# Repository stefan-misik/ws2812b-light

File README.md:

# WS2812b Christmas Lights

This is a simple WS2812b Christmas lights controller using ATtiny85 microcontroller.

## Hardware

## Results

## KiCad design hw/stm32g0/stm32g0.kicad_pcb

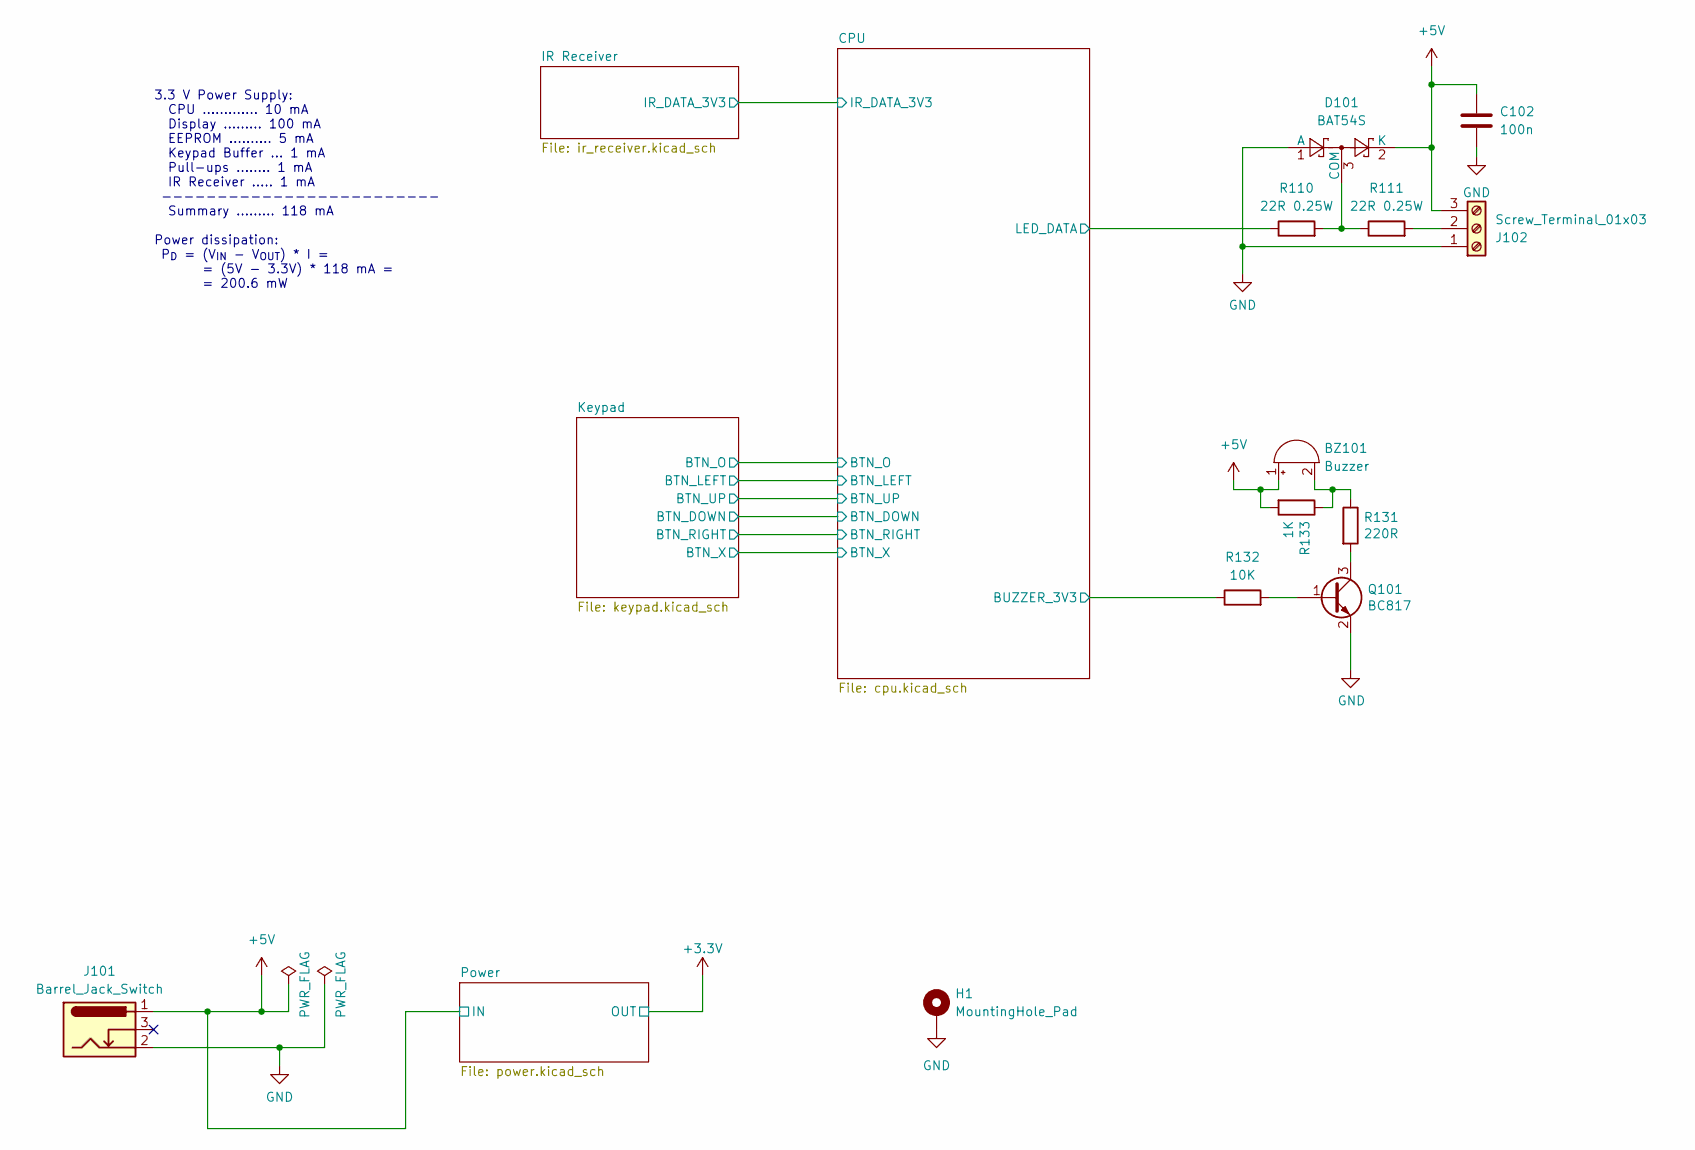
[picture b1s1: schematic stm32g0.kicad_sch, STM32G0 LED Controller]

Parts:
BZ101: Buzzer; Buzzer_Stacked
C102: 100n; C_0805_2012Metric_Pad1.18x1.45mm_HandSolder
D101: BAT54S; SOT-23_Handsoldering
H1: MountingHole_Pad; MountingHole_2.5mm_Pad_TopBottom
J101: Barrel_Jack_Switch; BarrelJack_GCT_DCJ200-10-A_Horizontal
J102: Screw_Terminal_01x03; TerminalBlock_Phoenix_MKDS-1,5-3_1x03_P5.00mm_Horizontal
Q101: BC817; SOT-23_Handsoldering
R110, R111: 22R 0.25W; R_1206_3216Metric_Pad1.30x1.75mm_HandSolder
R131: 220R; R_0805_2012Metric_Pad1.20x1.40mm_HandSolder
R132: 10K; R_0805_2012Metric_Pad1.20x1.40mm_HandSolder
R133: 1K; R_0805_2012Metric_Pad1.20x1.40mm_HandSolder

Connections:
+5V: BZ101.1 (+), C102.1, D101.2 (K), J101.1, J102.3, R133.2; also elsewhere on the board
/CPU/BUZZER_3V3: R132.1; also elsewhere on the board
/CPU/LED_DATA: R110.1; also elsewhere on the board
GND: C102.2, D101.1 (A), H1.1, J101.2, J102.1, Q101.2 (E); also elsewhere on the board
unnamed: BZ101.2 (-), R131.1, R133.1
unnamed: D101.3 (COM), R110.2, R111.1
unnamed: J102.2, R111.2
unnamed: Q101.1 (B), R132.2
unnamed: Q101.3 (C), R131.2

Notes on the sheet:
3.3 V Power Supply: CPU ............. 10 mA Display ......... 100 mA EEPROM .......... 5 mA Keypad Buffer ... 1 mA Pull-ups ........ 1 mA IR Receiver ..... 1 mA ------------------------- Summary ......... 118 mA Power dissipation: P_{D} = (V_{IN} - V_{OUT}) * I = = (5V - 3.3V) * 118 mA = = 200.6 mW

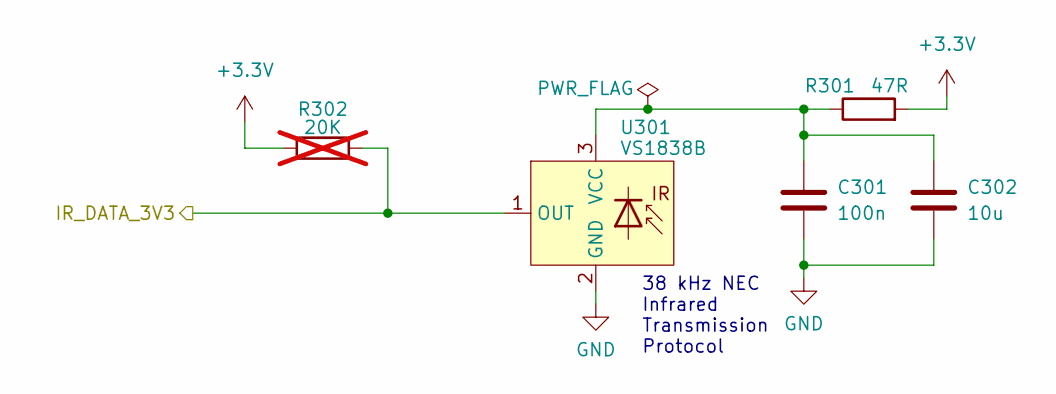
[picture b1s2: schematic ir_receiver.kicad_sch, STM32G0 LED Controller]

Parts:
C301: 100n; C_0805_2012Metric_Pad1.18x1.45mm_HandSolder
C302: 10u; C_1206_3216Metric_Pad1.33x1.80mm_HandSolder
R301: 47R; R_0805_2012Metric_Pad1.20x1.40mm_HandSolder
R302: 20K; R_0805_2012Metric_Pad1.20x1.40mm_HandSolder; not fitted
U301: VS1838B; PinSocket_1x03_P2.54mm_Vertical

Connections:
+3.3V: R301.2, R302.2; also elsewhere on the board
/CPU/IR_DATA_3V3: R302.1, U301.1 (OUT); also elsewhere on the board
GND: C301.2, C302.2, U301.2 (GND); also elsewhere on the board
unnamed: C301.1, C302.1, R301.1, U301.3 (VCC)

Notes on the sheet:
38 kHz NEC Infrared Transmission Protocol

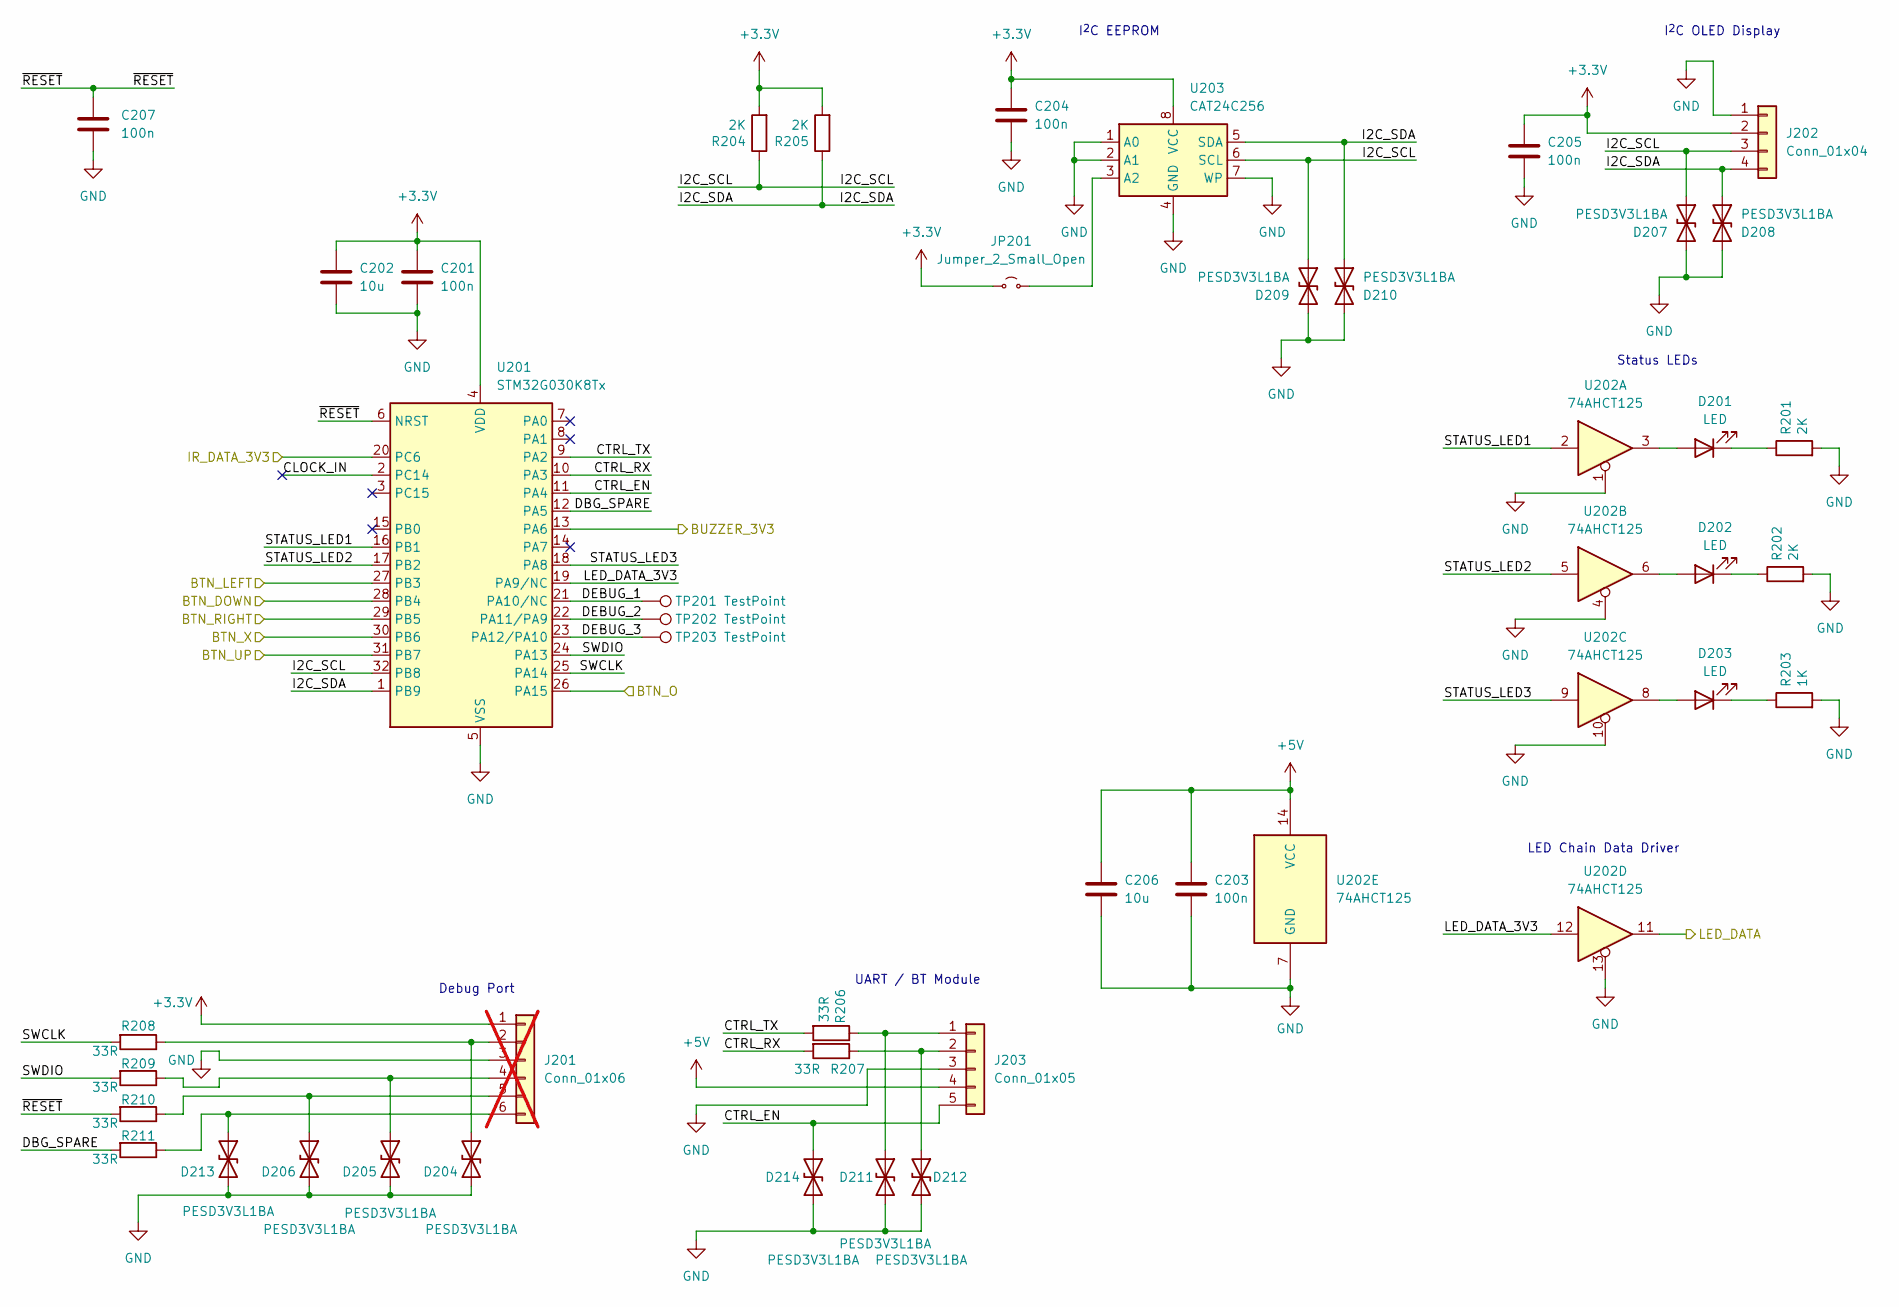
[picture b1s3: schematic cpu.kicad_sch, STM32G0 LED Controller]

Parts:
C201, C203, C204, C205, C207: 100n; C_0805_2012Metric_Pad1.18x1.45mm_HandSolder
C202, C206: 10u; C_1206_3216Metric_Pad1.33x1.80mm_HandSolder
D201, D202, D203: LED; LED_0805_2012Metric_Pad1.15x1.40mm_HandSolder
D204, D205, D206, D207, D208, D209, D210, D211, D212, D213, D214: PESD3V3L1BA; D_SOD-323_HandSoldering
J201: Conn_01x06; PinHeader_1x06_P2.54mm_Vertical; not fitted
J202: Conn_01x04; PinSocket_1x04_P2.54mm_Vertical
J203: Conn_01x05; PinSocket_1x05_P2.54mm_Vertical
JP201: Jumper_2_Small_Open; SolderJumper-2_P1.3mm_Open_RoundedPad1.0x1.5mm
R201, R202, R204, R205: 2K; R_0805_2012Metric_Pad1.20x1.40mm_HandSolder
R203: 1K; R_0805_2012Metric_Pad1.20x1.40mm_HandSolder
R206, R207, R208, R209, R210, R211: 33R; R_0805_2012Metric_Pad1.20x1.40mm_HandSolder
TP201, TP202, TP203: TestPoint; TestPoint_Pad_1.0x1.0mm
U201: STM32G030K8Tx; LQFP-32_7x7mm_P0.8mm
U202: 74AHCT125; SOIC-14_3.9x8.7mm_P1.27mm
U203: CAT24C256; DIP-8_W7.62mm_Socket_Stacked_SOIC-8_3.9x4.9mm_P1.27mm

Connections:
+3.3V: C201.1, C202.1, C204.1, C205.1, J201.1, J202.2, JP201.1 (A), R204.2, R205.2, U201.4 (VDD), U203.8 (VCC); also elsewhere on the board
+5V: C203.1, C206.1, J203.4, U202.14 (VCC); also elsewhere on the board
/CPU/BTN_DOWN: U201.28 (PB4); also elsewhere on the board
/CPU/BTN_LEFT: U201.27 (PB3); also elsewhere on the board
/CPU/BTN_O: U201.26 (PA15); also elsewhere on the board
/CPU/BTN_RIGHT: U201.29 (PB5); also elsewhere on the board
/CPU/BTN_UP: U201.31 (PB7); also elsewhere on the board
/CPU/BTN_X: U201.30 (PB6); also elsewhere on the board
/CPU/BUZZER_3V3: U201.13 (PA6); also elsewhere on the board
/CPU/CLOCK_IN: U201.2 (PC14)
/CPU/CTRL_EN: D214.1 (A1), J203.5, U201.11 (PA4)
/CPU/CTRL_RX: R207.2, U201.10 (PA3)
/CPU/CTRL_TX: R206.2, U201.9 (PA2)
/CPU/DBG_SPARE: R211.2, U201.12 (PA5)
/CPU/DEBUG_1: TP201.1, U201.21 (PA10/NC)
/CPU/DEBUG_2: TP202.1, U201.22 (PA11/PA9)
/CPU/DEBUG_3: TP203.1, U201.23 (PA12/PA10)
/CPU/I2C_SCL: D207.1 (A1), D209.1 (A1), J202.3, R204.1, U201.32 (PB8), U203.6 (SCL)
/CPU/I2C_SDA: D208.1 (A1), D210.1 (A1), J202.4, R205.1, U201.1 (PB9), U203.5 (SDA)
/CPU/IR_DATA_3V3: U201.20 (PC6); also elsewhere on the board
/CPU/LED_DATA: U202.11; also elsewhere on the board
/CPU/LED_DATA_3V3: U201.19 (PA9/NC), U202.12
/CPU/STATUS_LED1: U201.16 (PB1), U202.2
/CPU/STATUS_LED2: U201.17 (PB2), U202.5
/CPU/STATUS_LED3: U201.18 (PA8), U202.9
/CPU/SWCLK: R208.2, U201.25 (PA14)
/CPU/SWDIO: R209.2, U201.24 (PA13)
/CPU/~RESET: C207.1, R210.2, U201.6 (NRST)
GND: C201.2, C202.2, C203.2, C204.2, C205.2, C206.2, C207.2, D204.2 (A2), D205.2 (A2), D206.2 (A2), D207.2 (A2), D208.2 (A2), D209.2 (A2), D210.2 (A2), D211.2 (A2), D212.2 (A2), D213.2 (A2), D214.2 (A2), J201.3, J202.1, J203.3, R201.2, R202.2, R203.2, U201.5 (VSS), U202.1, U202.4, U202.7 (GND), U202.10, U202.13, U203.1 (A0), U203.2 (A1), U203.4 (GND), U203.7 (WP); also elsewhere on the board
unnamed: D201.2 (A), U202.3
unnamed: D201.1 (K), R201.1
unnamed: D202.2 (A), U202.6
unnamed: D202.1 (K), R202.1
unnamed: D203.2 (A), U202.8
unnamed: D203.1 (K), R203.1
unnamed: D204.1 (A1), J201.2, R208.1
unnamed: D205.1 (A1), J201.4, R209.1
unnamed: D206.1 (A1), J201.5, R210.1
unnamed: D211.1 (A1), J203.1, R206.1
unnamed: D212.1 (A1), J203.2, R207.1
unnamed: D213.1 (A1), J201.6, R211.1
unnamed: JP201.2 (B), U203.3 (A2)

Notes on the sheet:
Status LEDs
LED Chain Data Driver
I^{2}C EEPROM
Debug Port
I^{2}C OLED Display
UART / BT Module

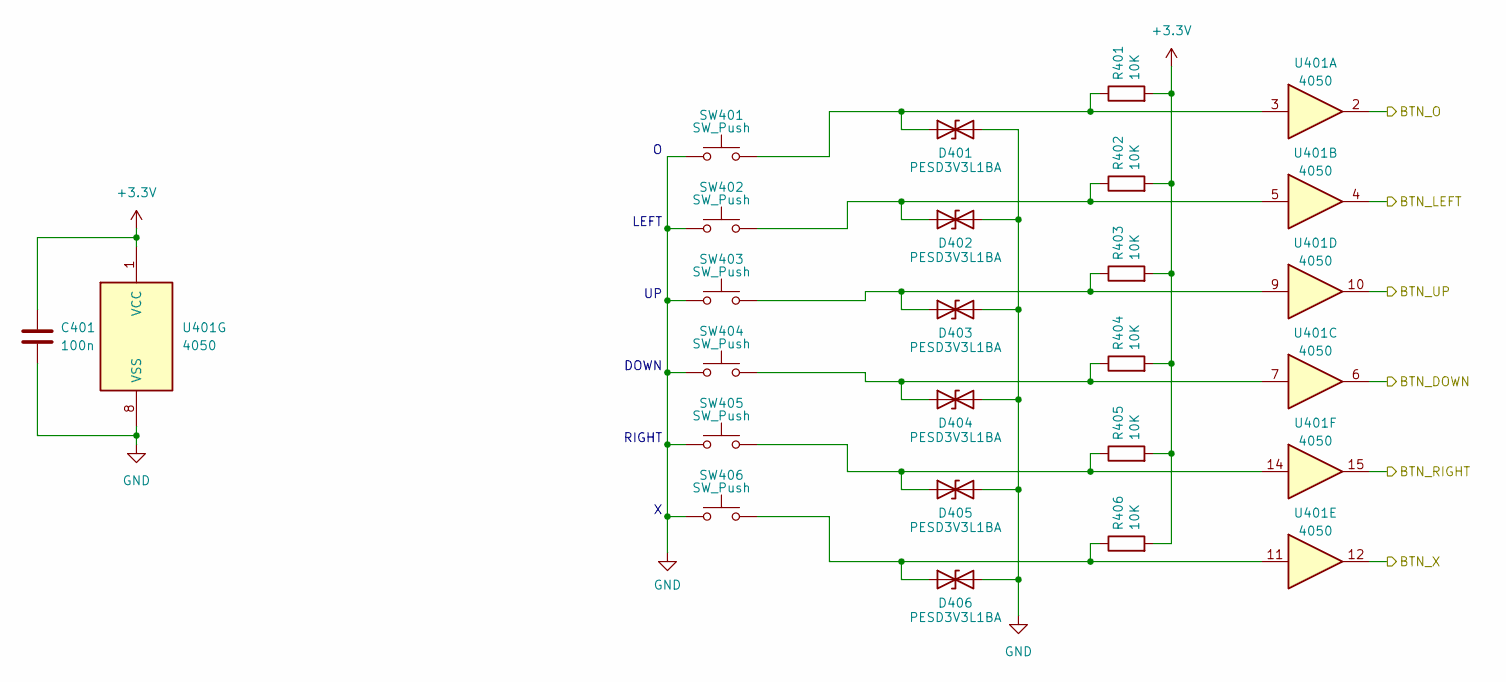
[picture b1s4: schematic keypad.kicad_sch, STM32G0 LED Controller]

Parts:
C401: 100n; C_0805_2012Metric_Pad1.18x1.45mm_HandSolder
D401, D402, D403, D404, D405, D406: PESD3V3L1BA; D_SOD-323_HandSoldering
R401, R402, R403, R404, R405, R406: 10K; R_0805_2012Metric_Pad1.20x1.40mm_HandSolder
SW401, SW402, SW403, SW404, SW405, SW406: SW_Push; SW_PUSH_6mm
U401: 4050; SOIC-16_3.9x9.9mm_P1.27mm

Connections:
+3.3V: C401.1, R401.2, R402.2, R403.2, R404.2, R405.2, R406.2, U401.1 (VCC); also elsewhere on the board
/CPU/BTN_DOWN: U401.6; also elsewhere on the board
/CPU/BTN_LEFT: U401.4; also elsewhere on the board
/CPU/BTN_O: U401.2; also elsewhere on the board
/CPU/BTN_RIGHT: U401.15; also elsewhere on the board
/CPU/BTN_UP: U401.10; also elsewhere on the board
/CPU/BTN_X: U401.12; also elsewhere on the board
GND: C401.2, D401.2 (A2), D402.2 (A2), D403.2 (A2), D404.2 (A2), D405.2 (A2), D406.2 (A2), SW401.1, SW402.1, SW403.1, SW404.1, SW405.1, SW406.1, U401.8 (VSS); also elsewhere on the board
unnamed: D401.1 (A1), R401.1, SW401.2, U401.3
unnamed: D402.1 (A1), R402.1, SW402.2, U401.5
unnamed: D403.1 (A1), R403.1, SW403.2, U401.9
unnamed: D404.1 (A1), R404.1, SW404.2, U401.7
unnamed: D405.1 (A1), R405.1, SW405.2, U401.14
unnamed: D406.1 (A1), R406.1, SW406.2, U401.11

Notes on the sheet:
RIGHT
LEFT
DOWN

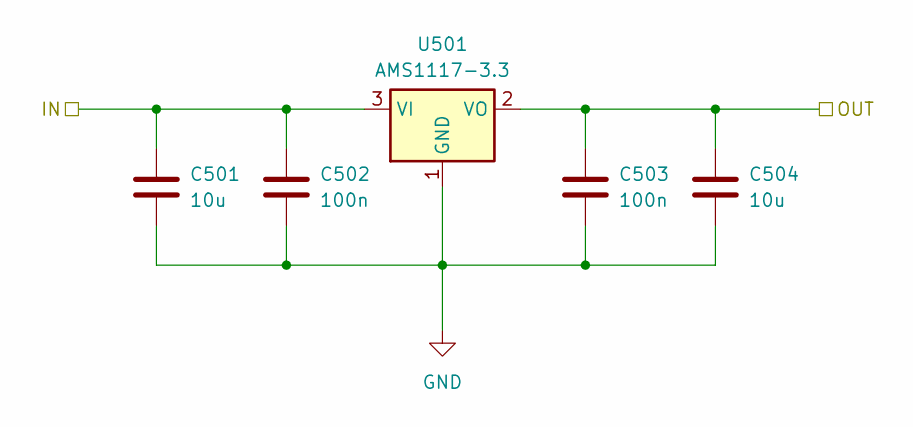
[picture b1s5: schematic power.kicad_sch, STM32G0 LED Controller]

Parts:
C501, C504: 10u; C_1206_3216Metric_Pad1.33x1.80mm_HandSolder
C502, C503: 100n; C_0805_2012Metric_Pad1.18x1.45mm_HandSolder
U501: AMS1117-3.3; SOT-223-3_TabPin2

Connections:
+3.3V: C503.1, C504.1, U501.2 (VO); also elsewhere on the board
+5V: C501.1, C502.1, U501.3 (VI); also elsewhere on the board
GND: C501.2, C502.2, C503.2, C504.2, U501.1 (GND); also elsewhere on the board

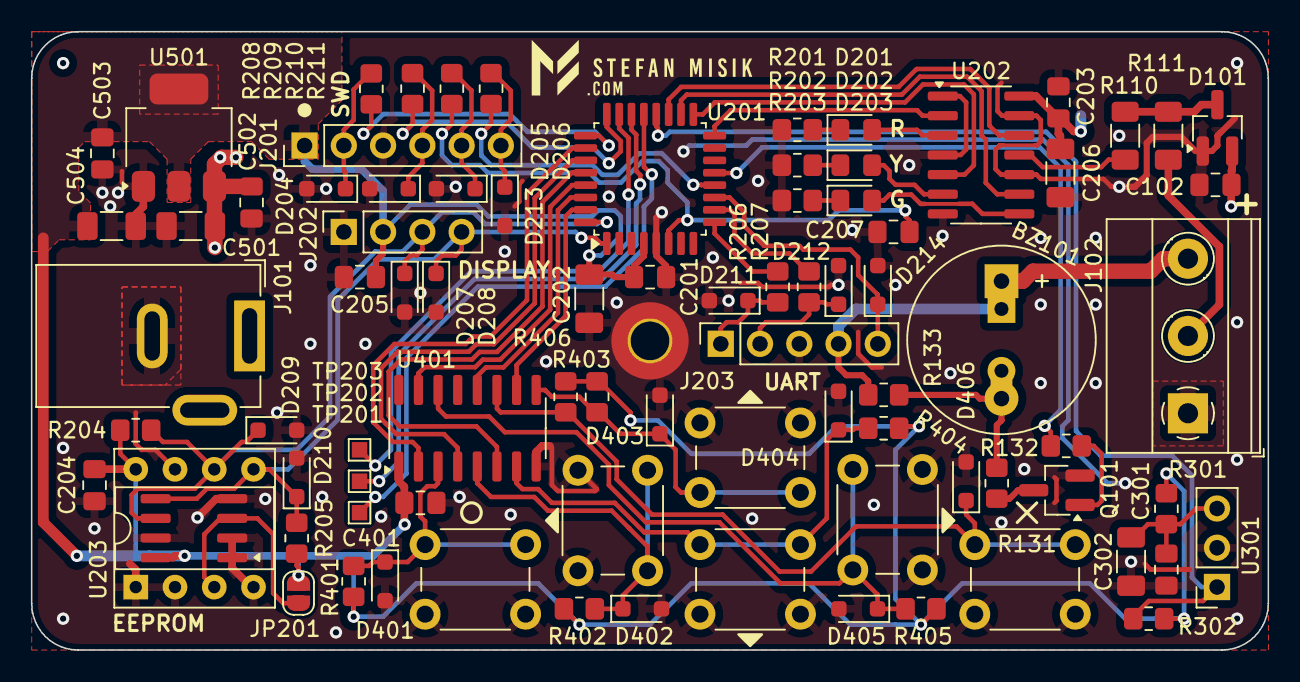
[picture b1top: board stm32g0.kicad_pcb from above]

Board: 4 copper layers, 80.0 x 40.0 mm, 84 parts (0 on the bottom side), 53 nets.

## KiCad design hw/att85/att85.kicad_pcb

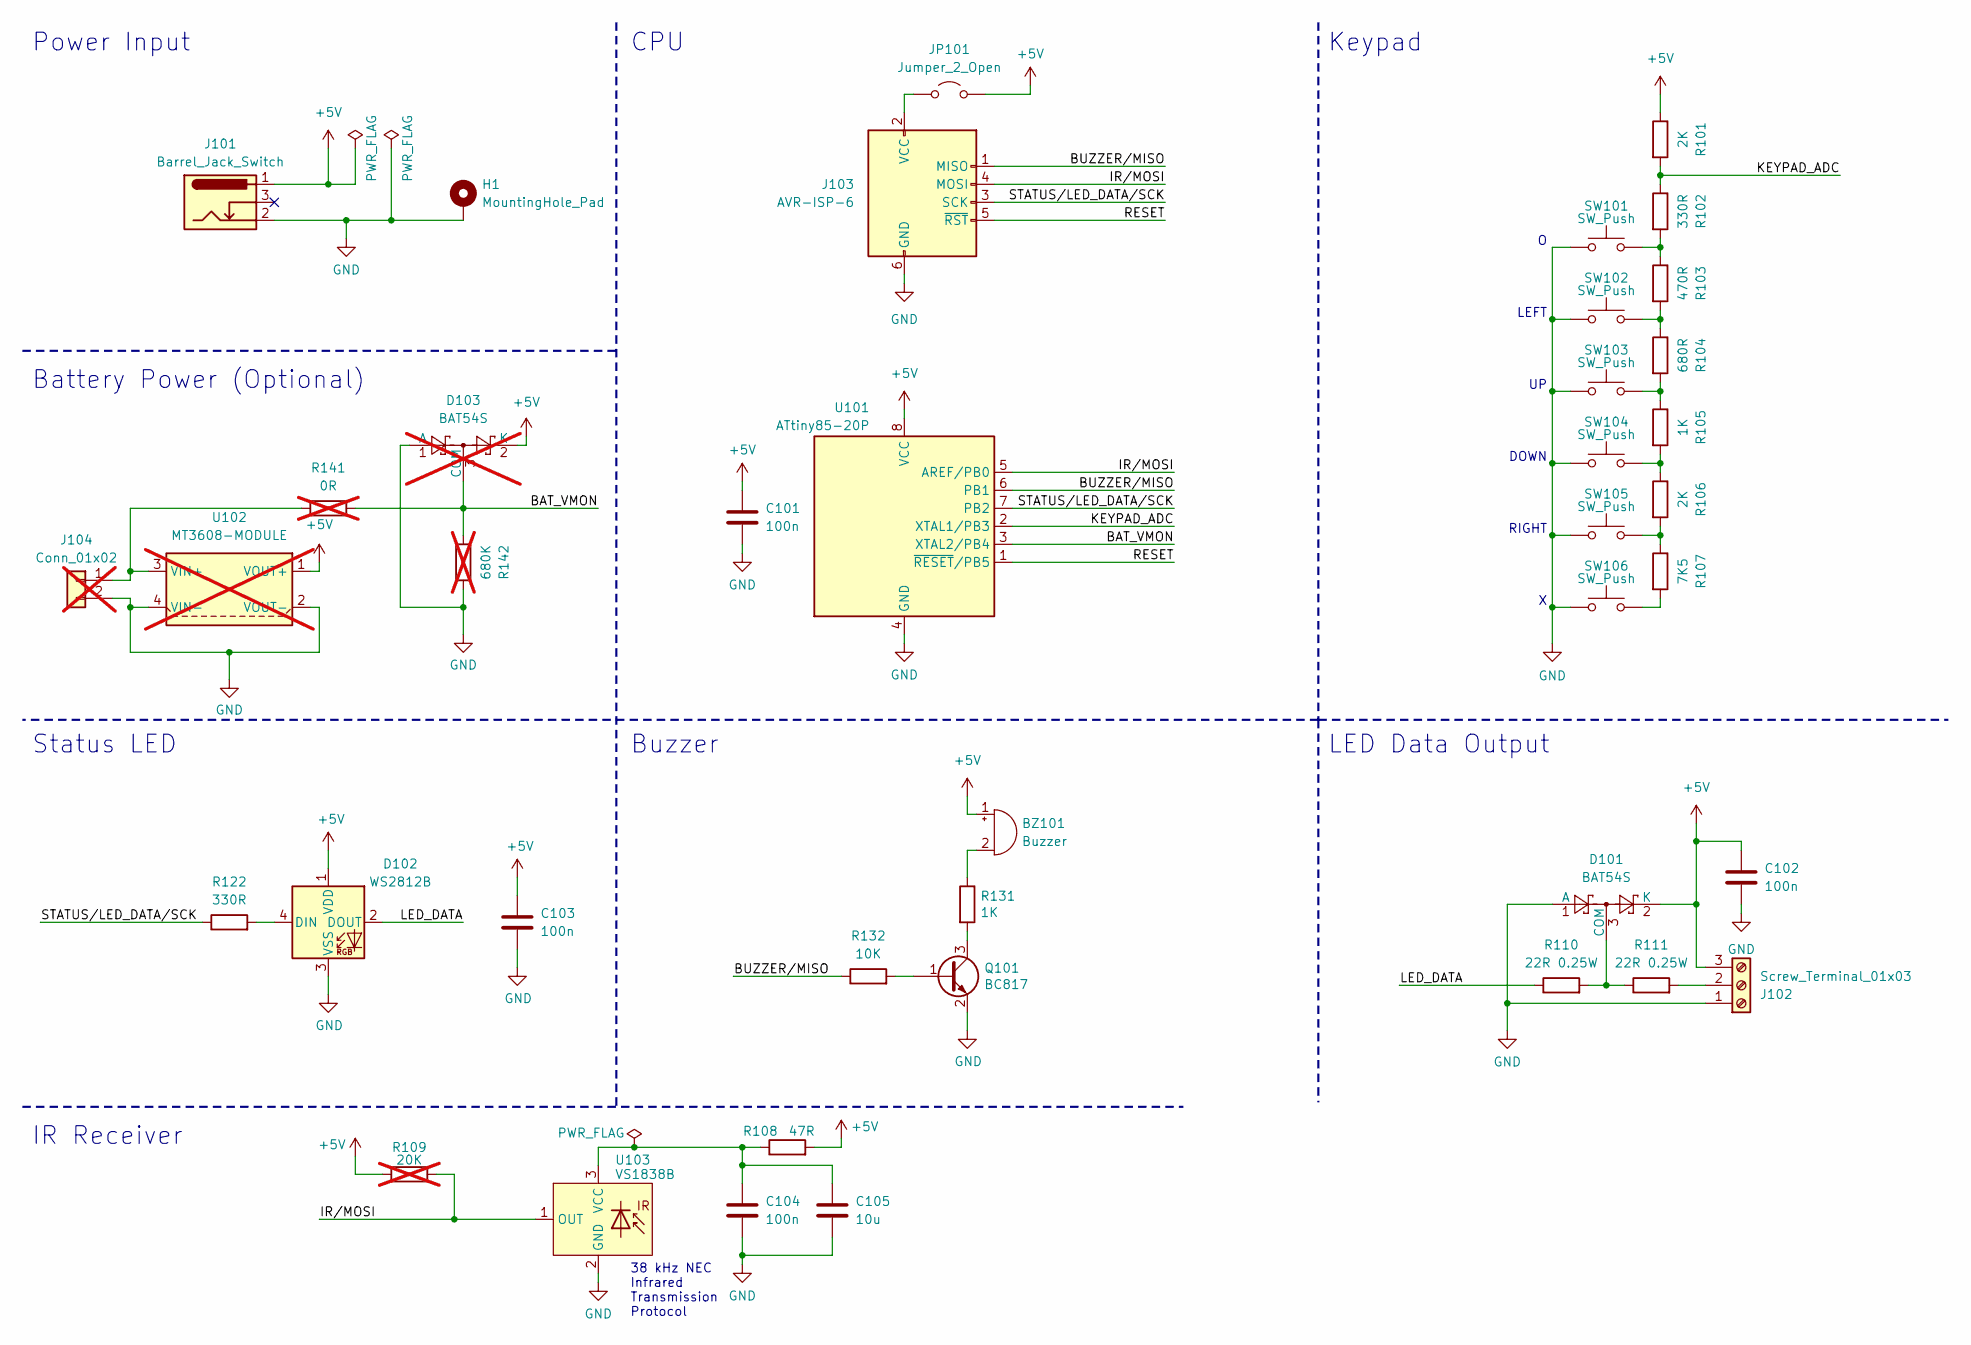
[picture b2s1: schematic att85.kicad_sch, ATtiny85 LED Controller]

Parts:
BZ101: Buzzer; Buzzer_Stacked
C101, C102, C103, C104: 100n; C_0805_2012Metric_Pad1.18x1.45mm_HandSolder
C105: 10u; C_1206_3216Metric_Pad1.33x1.80mm_HandSolder
D101: BAT54S; SOT-23
D102: WS2812B; LED_WS2812B_PLCC4_5.0x5.0mm_P3.2mm
D103: BAT54S; SOT-23; not fitted
H1: MountingHole_Pad; MountingHole_2.5mm_Pad_TopBottom
J101: Barrel_Jack_Switch; BarrelJack_GCT_DCJ200-10-A_Horizontal
J102: Screw_Terminal_01x03; TerminalBlock_Phoenix_MKDS-1,5-3_1x03_P5.00mm_Horizontal
J103: AVR-ISP-6; IDC-Header_2x03_P2.54mm_Vertical
J104: Conn_01x02; JST_PH_B2B-PH-K_1x02_P2.00mm_Vertical; not fitted
JP101: Jumper_2_Open; PinHeader_1x02_P2.54mm_Vertical
Q101: BC817; SOT-23_Handsoldering
R101, R106: 2K; R_0805_2012Metric_Pad1.20x1.40mm_HandSolder
R102, R122: 330R; R_0805_2012Metric_Pad1.20x1.40mm_HandSolder
R103: 470R; R_0805_2012Metric_Pad1.20x1.40mm_HandSolder
R104: 680R; R_0805_2012Metric_Pad1.20x1.40mm_HandSolder
R105, R131: 1K; R_0805_2012Metric_Pad1.20x1.40mm_HandSolder
R107: 7K5; R_0805_2012Metric_Pad1.20x1.40mm_HandSolder
R108: 47R; R_0805_2012Metric_Pad1.20x1.40mm_HandSolder
R109: 20K; R_0805_2012Metric_Pad1.20x1.40mm_HandSolder; not fitted
R110, R111: 22R 0.25W; R_1206_3216Metric_Pad1.30x1.75mm_HandSolder
R132: 10K; R_0805_2012Metric_Pad1.20x1.40mm_HandSolder
R141: 0R; R_0805_2012Metric_Pad1.20x1.40mm_HandSolder_Jumper; not fitted
R142: 680K; R_0805_2012Metric_Pad1.20x1.40mm_HandSolder; not fitted
SW101, SW102, SW103, SW104, SW105, SW106: SW_Push; SW_PUSH_6mm
U101: ATtiny85-20P; DIP-8_W7.62mm
U102: MT3608-MODULE; mt3608-module; not fitted
U103: VS1838B; PinSocket_1x03_P2.54mm_Vertical

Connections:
+5V: BZ101.1 (+), C101.1, C102.1, C103.1, D101.2 (K), D102.1 (VDD), D103.2 (K), J101.1, J102.3, JP101.2 (B), R101.1, R108.2, R109.2, U101.8 (VCC), U102.1 (VOUT+)
/BAT_VMON: D103.3 (COM), R141.2, R142.1, U101.3 (XTAL2/PB4)
/BUZZER/MISO: J103.1 (MISO), R132.1, U101.6 (PB1)
/IR/MOSI: J103.4 (MOSI), R109.1, U101.5 (AREF/PB0), U103.1 (OUT)
/KEYPAD_ADC: R101.2, R102.1, U101.2 (XTAL1/PB3)
/LED_DATA: D102.2 (DOUT), R110.1
/RESET: J103.5 (~RST), U101.1 (~RESET/PB5)
/STATUS/LED_DATA/SCK: J103.3 (SCK), R122.1, U101.7 (PB2)
GND: C101.2, C102.2, C103.2, C104.2, C105.2, D101.1 (A), D102.3 (VSS), D103.1 (A), H1.1, J101.2, J102.1, J103.6 (GND), J104.2, Q101.2 (E), R142.2, SW101.1, SW102.1, SW103.1, SW104.1, SW105.1, SW106.1, U101.4 (GND), U102.2 (VOUT-), U102.4 (VIN-), U103.2 (GND)
unnamed: BZ101.2 (-), R131.1
unnamed: D101.3 (COM), R110.2, R111.1
unnamed: D102.4 (DIN), R122.2
unnamed: J102.2, R111.2
unnamed: J103.2 (VCC), JP101.1 (A)
unnamed: J104.1, R141.1, U102.3 (VIN+)
unnamed: Q101.1 (B), R132.2
unnamed: Q101.3 (C), R131.2
unnamed: R102.2, R103.1, SW101.2
unnamed: R103.2, R104.1, SW102.2
unnamed: R104.2, R105.1, SW103.2
unnamed: R105.2, R106.1, SW104.2
unnamed: R106.2, R107.1, SW105.2
unnamed: R107.2, SW106.2
unnamed: C104.1, C105.1, R108.1, U103.3 (VCC)

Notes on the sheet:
CPU
LED Data Output
RIGHT
Battery Power (Optional)
LEFT
Keypad
DOWN
38 kHz NEC Infrared Transmission Protocol
Buzzer
Status LED
IR Receiver
Power Input

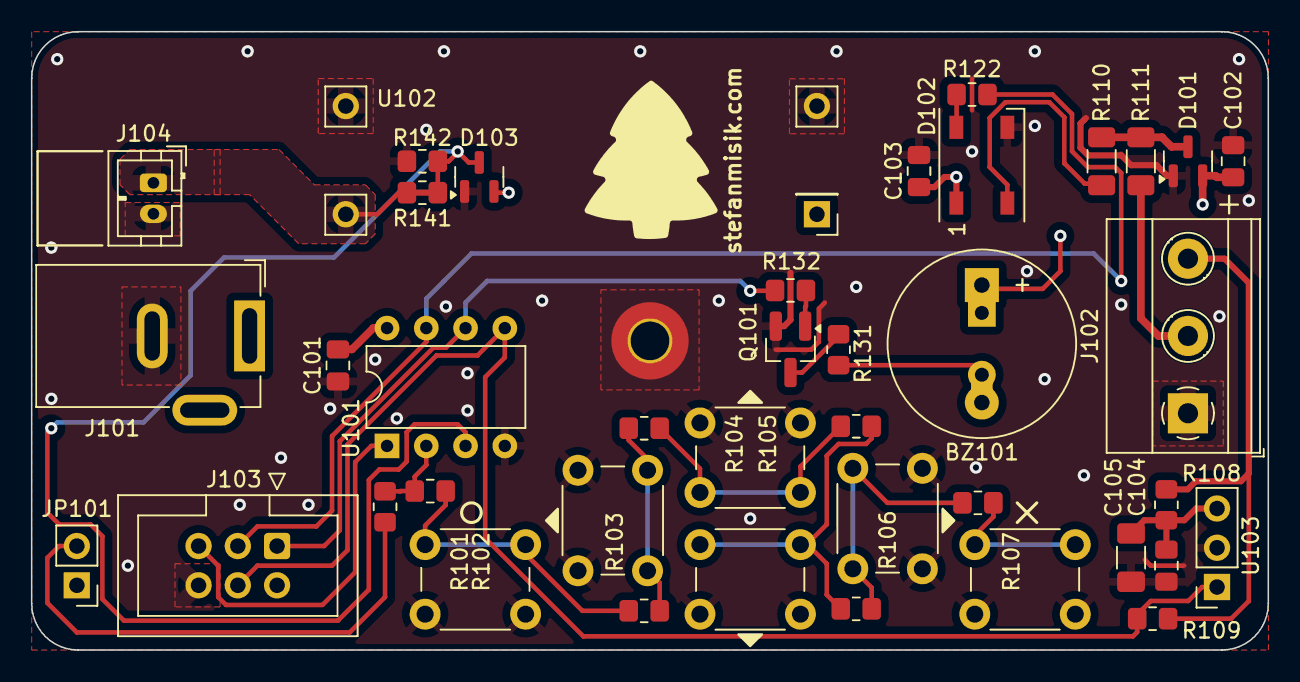
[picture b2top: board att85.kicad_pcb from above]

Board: 2 copper layers, 80.0 x 40.0 mm, 41 parts (0 on the bottom side), 24 nets.

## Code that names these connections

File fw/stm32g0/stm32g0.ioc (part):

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Mcu.Name=STM32G070KBTx
Mcu.Package=LQFP32
Mcu.UserName=STM32G070KBTx
PA10.GPIOParameters=GPIO_Label
PA10.GPIO_Label=DEBUG_1
PA10.Signal=GPIO_Output
PA11\ [PA9].GPIOParameters=GPIO_Label
PA11\ [PA9].GPIO_Label=DEBUG_2
PA11\ [PA9].Signal=GPIO_Output
PA12\ [PA10].GPIOParameters=GPIO_Label
PA12\ [PA10].GPIO_Label=DEBUG_3
PA12\ [PA10].Signal=GPIO_Output
PA13.Mode=Serial_Wire
PA13.Signal=SYS_SWDIO
PA14-BOOT0.Mode=Serial_Wire
PA14-BOOT0.Signal=SYS_SWCLK
PA15.GPIOParameters=GPIO_Label
PA15.GPIO_Label=BTN_O
PA15.Signal=GPIO_Input
PA2.GPIOParameters=GPIO_Label
PA2.GPIO_Label=CTRL_TX
PA2.Mode=Asynchronous
PA2.Signal=USART2_TX
PA3.GPIOParameters=GPIO_Label
PA3.GPIO_Label=CTRL_RX
PA3.Mode=Asynchronous
PA3.Signal=USART2_RX
PA4.GPIOParameters=GPIO_Label
PA4.GPIO_Label=CTRL_EN
PA4.Signal=GPIO_Output
PA5.GPIOParameters=GPIO_Label
PA5.GPIO_Label=DEBUG_PORT_SPARE
PA5.Signal=USART3_TX
PA6.GPIOParameters=GPIO_Label
PA6.GPIO_Label=BUZZER
PA6.Signal=S_TIM16_CH1
PA8.GPIOParameters=GPIO_Label
PA8.GPIO_Label=STATUS_LED3
PA8.Signal=GPIO_Output
PA9.GPIOParameters=GPIO_Label
PA9.GPIO_Label=LED_DATA
PA9.Signal=S_TIM1_CH2
PB1.GPIOParameters=GPIO_Label
PB1.GPIO_Label=STATUS_LED1
PB1.Signal=GPIO_Output
PB2.GPIOParameters=GPIO_Label
PB2.GPIO_Label=STATUS_LED2
PB2.Signal=GPIO_Output
PB3.GPIOParameters=GPIO_Label
PB3.GPIO_Label=BTN_LEFT
PB3.Signal=GPIO_Input
PB4.GPIOParameters=GPIO_Label
PB4.GPIO_Label=BTN_DOWN
PB4.Signal=GPIO_Input
PB5.GPIOParameters=GPIO_Label
PB5.GPIO_Label=BTN_RIGHT
PB5.Signal=GPIO_Input
PB6.GPIOParameters=GPIO_Label
PB6.GPIO_Label=BTN_X
PB6.Signal=GPIO_Input
PB7.GPIOParameters=GPIO_Label
PB7.GPIO_Label=BTN_UP
PB7.Signal=GPIO_Input
PB8.Mode=I2C
PB8.Signal=I2C1_SCL
PB9.Mode=I2C
PB9.Signal=I2C1_SDA
PC14-OSC32_IN\ (PC14).Mode=HSE-External-Clock-Source
PC14-OSC32_IN\ (PC14).Signal=RCC_OSC_IN
PC6.GPIOParameters=GPIO_Label
PC6.GPIO_Label=IR_DATA
PC6.Signal=S_TIM3_CH1
RCC.HSE_VALUE=8000000
RCC.SYSCLKFreq_VALUE=64000000
RCC.SYSCLKSource=RCC_SYSCLKSOURCE_PLLCLK
board=custom

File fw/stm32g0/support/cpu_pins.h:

/**
 * @file
 */

#ifndef SUPPORT_CPU_PINS_H_
#define SUPPORT_CPU_PINS_H_

#include "stm32g0xx_ll_gpio.h"


#define CTRL_TX_Pin LL_GPIO_PIN_2
#define CTRL_TX_GPIO_Port GPIOA
#define CTRL_RX_Pin LL_GPIO_PIN_3
#define CTRL_RX_GPIO_Port GPIOA
#define CTRL_EN_Pin LL_GPIO_PIN_4
#define CTRL_EN_GPIO_Port GPIOA
#define BUZZER_Pin LL_GPIO_PIN_6
#define BUZZER_GPIO_Port GPIOA
#define STATUS_LED1_Pin LL_GPIO_PIN_1
#define STATUS_LED1_GPIO_Port GPIOB
#define STATUS_LED2_Pin LL_GPIO_PIN_2
#define STATUS_LED2_GPIO_Port GPIOB
#define STATUS_LED3_Pin LL_GPIO_PIN_8
#define STATUS_LED3_GPIO_Port GPIOA
#define LED_DATA_Pin LL_GPIO_PIN_9
#define LED_DATA_GPIO_Port GPIOA
#define IR_DATA_Pin LL_GPIO_PIN_6
#define IR_DATA_GPIO_Port GPIOC
#define DEBUG_1_Pin LL_GPIO_PIN_10
#define DEBUG_1_GPIO_Port GPIOA
#define DEBUG_2_Pin LL_GPIO_PIN_11
#define DEBUG_2_GPIO_Port GPIOA
#define DEBUG_3_Pin LL_GPIO_PIN_12
#define DEBUG_3_GPIO_Port GPIOA
#define BTN_O_Pin LL_GPIO_PIN_15
#define BTN_O_GPIO_Port GPIOA
#define BTN_LEFT_Pin LL_GPIO_PIN_3
#define BTN_LEFT_GPIO_Port GPIOB
#define BTN_DOWN_Pin LL_GPIO_PIN_4
#define BTN_DOWN_GPIO_Port GPIOB
#define BTN_RIGHT_Pin LL_GPIO_PIN_5
#define BTN_RIGHT_GPIO_Port GPIOB
#define BTN_X_Pin LL_GPIO_PIN_6
#define BTN_X_GPIO_Port GPIOB
#define BTN_UP_Pin LL_GPIO_PIN_7
#define BTN_UP_GPIO_Port GPIOB
#define I2C_SCL_Pin LL_GPIO_PIN_8
#define I2C_SCL_GPIO_Port GPIOB
#define I2C_SDA_Pin LL_GPIO_PIN_9
#define I2C_SDA_GPIO_Port GPIOB
#define TRACE_Pin LL_GPIO_PIN_5
#define TRACE_GPIO_Port GPIOA



#endif  // SUPPORT_CPU_PINS_H_

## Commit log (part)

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2023-12-31 chore: add EEPROM buffer tool
2023-12-31 feat: extend time counter bit-length
2023-12-31 refactor: handle new warnings
2023-12-31 feat: add NVM storage class
2024-01-02 chore(hw): add battery power supply
2024-01-02 chore(hw): add communication slot
2024-01-02 chore(hw): finish first version of the layout
2024-01-04 chore(hw): improve layout
2024-01-06 chore(hw): switch status LED for WS2812B
2024-01-06 chore(hw): layout improvements
2024-01-06 chore(hw): move battery connector
2024-01-07 feat(hw): add IR receiver
2024-01-08 chore(hw): add separate divider position for IR receiver
2024-01-08 chore(hw): remove UART RX, allow buzzer to be disconnected
2024-01-09 refactor(hw): improve keypad divider layout
2024-01-10 refactor(hw): change CPU footprint and 3D model
2024-01-12 chore(hw): move buzzer connection, update layout
2024-01-12 chore(hw): produce gerber files
2024-01-14 docs(hw): update PCB image
2024-01-17 chore(fw): add analog input driver initialization
2024-02-02 chore(fw): add simple analog keypad readout
2024-02-02 refactor(hw): improve layout
2024-02-02 fix(fw): do not allow black color in color animation
2024-02-02 chore(fw): disable NVM storage handling for now
2024-02-03 chore(fw): make logical button order to reflect button priority
2024-02-04 chore(fw): add status LED support
2024-02-04 refactor(hw): make bit counting more natural
2024-02-22 fix(fw): do not reset color animation on animation start
2024-02-25 refactor(fw): switch to Timer 0 for internal timing
2024-02-28 feat(fw): add simple tone tester
2024-03-04 refactor(fw): prepare music element format
2024-05-07 chore(fw): add ID selector tool
2024-05-07 chore(fw): add first song for testing
2024-05-07 chore(fw): implement simple song player
2024-05-15 feat(fw): add simple song player
2024-05-16 chore(fw): add animation storage object
    This will replace Animation List and only current animation will be
    instantiated at a time.
2024-05-19 refactor(fw): optimize RAM usage
2024-05-21 refactor(fw): pass event flags to animations instead button actions directly
2024-05-21 feat(fw): implement music-based retro animation
2024-05-24 chore(fw): add script to generate songs
2024-05-24 build(fw): switch to generating songs
2024-05-26 feat(fw): add music loops
2024-06-01 build(fw): switch to -Os optimization
2024-06-01 feat(fw): add IR receiver code
2024-06-01 feat(fw): switch to exclusively using PB0 for IR receiver
    This change requires jumper JP103 (one near uC) to be re-jumped.
    This change was done due to the fact that ADC value can not be used to
    detect the start of the IR transmission, as the value read is delayed by
    ~8ms.
2024-06-02 refactor(fw): move IR receiver code to separate file
2024-06-02 feat(hw): remove unused components, wire IR to separate uC pin
2024-06-02 refactor(hw): move to Kicad v8
2024-06-02 fix(fw): fix IR receive repeat
2024-06-02 fix(fw): fix recovery from IR receiver blocking the execution
2024-06-02 refactor(fw): extract IR reception code
2024-06-02 fix(fw): disable interrupts when receiving IR command
2024-06-02 fix(hw): minor improvements
2024-06-02 refactor(hw): add rounded corners
2024-06-03 fix(hw): move IR receiver resistor according the datasheet
2024-06-06 fix(hw): minor fixes
2024-06-12 build(fw): do not include dependency files when cleaning
2024-06-17 chore(hw): add STM32 CPU
2024-06-19 chore(hw): update debug port pinout
2024-06-19 chore(hw): organize schematics into sheets, sync with layout
2024-06-20 chore(hw): wired basic connections, organized main sheet
2024-06-21 chore(hw): resize power rail
2024-06-21 chore(hw): add dedicated GND rails
2024-06-22 chore(hw): connect IR data CPU pin
2024-06-24 chore(hw): add peripheral connections, layout power supply
2024-06-25 chore(hw): prepare layout
2024-06-25 chore(hw): add buzzer connection
2024-06-25 chore(hw): partial layout
2024-06-26 chore(hw): move debug UART header
2024-06-26 chore(hw): rename project
2024-06-26 chore(hw): restore original ATtiny85 project
2024-06-26 chore(hw): clean-up fabrication scheme
2024-06-26 chore(hw): minor changes
2024-06-27 chore(hw): increase main power rail thickness
2024-06-27 chore(hw): add inner layer GND connections
2024-06-29 chore(hw): fix silkscreen
2024-06-29 chore(hw): remove unnecessary buzzer capacitor
2024-06-29 chore(fw): move ATtiny 85 code firmware code to separate directory
2024-06-30 build(fw): move build artifacts to separate directory
2024-06-30 chore(hw): tune the layout
2024-06-30 chore(hw): remove mounting hole thermal relief
2024-07-01 chore(hw): move ESD protection diode, minor layout tweaks
2024-07-02 chore(hw): add cable connector identifiers
2024-07-02 chore(hw): increase CPU decoupling
2024-07-03 chore(hw): change value of buzzer resistor
2024-07-03 chore(hw): improve silkscreen readability
2024-07-03 chore(hw): add stacked EEPROM footprint
2024-07-07 chore(fw): add stm32g0 IOC file
2024-07-09 chore(hw): add panelization makefiles
2024-07-09 chore(hw): remove JLC PCB order number location (now on panel frame)
2024-07-09 chore(hw): add fabrication files makefile rule
2024-07-09 chore(hw): organize F.Fab
2024-07-09 chore(hw): update PCB panel
2024-07-09 chore(hw): update debug stm32g0 debug port pinout
2024-07-11 chore(hw): general improvements, utilize some unused CPU pins
2024-07-13 chore(hw): improve layout, move NRST cap
2024-07-13 chore(hw): add BT module supply and control pins
2024-07-14 chore(hw): change debug port to pin header
2024-07-21 chore(hw): improve i2c layout
2024-07-21 chore(hw): add logos
2024-07-21 chore(hw): add version number
2024-07-21 chore(hw): change panel mouse bites
2024-07-21 chore(hw): improve debug port silkscreen marks
2024-07-22 chore(hw): fix debug port meander
2024-07-22 chore(hw): add keypad ESD protection
2024-07-22 chore(hw): minor fixes
2024-07-26 feat(fw): add support for multiple IR remotes
2024-08-01 chore(fw): create STM32G0 project
2024-08-08 docs(hw): add new hardware image
2024-08-09 chore(fw): add shared directory
2024-08-11 chore(fw): generate LED data using PWM proof of concept
2024-08-22 chore(fw): add LED driver DMA controller
2024-09-13 chore(fw): initialize DMAMUX
2024-10-05 chore(fw): add LED data reader
2024-10-10 chore(fw): implement DMA-driven LED update
2024-10-10 chore(fw): implement simple rainbow animation using STM32G0
2024-10-10 build(fw): allow extra warnings
2024-10-10 chore(fw): add LED correction
2024-10-15 chore(fw): add IR receiver driver
2024-10-18 chore(fw): clean-up DMA-driven LED controller
2024-10-18 chore(fw): add keypad driver
2024-10-27 chore(fw): add status LED driver
2024-11-02 perf(fw): improve button filter
2024-11-02 chore(fw): allow to use button filter without de-bouncing
2024-12-25 chore(fw): implement input source read-out
2025-01-11 chore(fw): compile-time configurable trace
2025-02-28 fix(fw): fix buzzer sometimes pausing when changing to higher note
2025-03-31 refactor(fw): use helper class for hidden private class data
2025-03-31 chore(fw): add animation interface for STM32G0
2025-07-05 chore(mech): implement box walls
2025-07-05 chore(mech): add PCB lock
2025-07-06 chore(mech): add PCB hooks
2025-07-06 chore(mech): add IO holes
2025-07-07 chore(mech): tune parameters
2025-07-07 chore(mech): add PCB mounting hole
2025-07-12 chore(mech): apply box modifications based on faults of real 3D print
2025-07-13 chore(mech): add top part
2025-07-20 chore(mech): use magnets to join top and bottom
2025-07-20 chore(mech): improve magnetic mating
2025-07-20 chore(mech): add top cover functional features
2025-07-21 chore(mech): add button holes
2025-08-03 fix(fw): prevent double-reporting IR remote button presses
2025-08-05 fix(fw): properly report newly pressed buttons
2025-08-05 fix(fw): remove dependency on deprecated code
2025-08-05 chore(fw): add key press processing by source
2025-08-05 refactor(fw): remove redundant IR receiver code
2025-08-08 chore(fw): implement key state processing
2025-08-08 chore(fw): add event queue
2025-08-10 build(fw): turn on -Werror in stm32g0 project
2025-08-11 refactor(fw): move demo animation inside proper interface
2025-08-11 feat(stm32g0): add CPU usage driver
2025-08-11 refactor(stm32g0): implement rainbow animation state state storage
2025-08-11 refactor(fw): make interface implementation final
2025-08-11 chore(stm32g0): implement serialization and de-serialization of animation state
2025-08-24 refactor(fw): clean-up ATT85 LED Controller
2025-08-24 feat(stm32g0): add I2C Bus driver
2025-08-24 refactor(stm32g0): move shared DMA code into common driver
2025-08-24 style(stm32g0): fix LED Correction code style
2025-08-24 I2C Test TODO squash this
2025-09-01 fix(stm32g0): fix broken release build
2025-10-01 fix(hw): make I2C pull-up stronger
2025-10-02 feat(stm32g0): remove I2C test code
2025-10-02 refactor(stm32g0): clean-up makefile
2025-10-06 refactor(stm32g0): use shared color tools in rainbow animation
2025-10-07 feat(stm32g0): add basic color animation
2025-10-07 feat(stm32g0): implement key event handling
2025-10-07 feat(stm32g0): implement rainbow animation configuration
2025-10-26 refactor(fw): fix spelling
2025-11-23 chore(stm32g0): switch to VS Code project
2025-11-23 refactor(stm32g0): add function for background tasks
2025-11-23 refactor(stm32g0): implement shared function for modifying animation parameters
2025-11-23 refactor(stm32g0): add other animation parameter setters/getters
2025-11-23 refactor(stm32g0): reuse parameter change function to change animations
2025-11-23 refactor(stm32g0): move main application code to a sub-directory
2025-11-23 refactor(stm32g0): fix typos
2025-11-23 feat(stm32g0): add shifting color animation
2025-11-23 feat(stm32g0): add twinkle animation
2025-11-23 refactor(stm32g0): switch to using concepts instead check<T>() helpers
2025-11-23 fix(stm32g0): ensure standard color array is in FLASH memory
2025-11-23 feat(stm32g0): leverage 32-bit MCU to improve color blending precision
2025-11-23 fix(fw): add missing default assignments and constructors
2025-11-24 chore: switch to VSCode workspace with other projects
2025-11-24 refactor: use .hpp for C++ headers in shared directory
2025-11-24 feat(stm32g0): add music
2025-11-24 refactor: move songs to shared directory
2025-11-24 refactor(stm32g0): use fixed-point offset in shifting color animation
2025-11-24 fix(stm32g0): fix buzzer whining after a note has done playing
2025-11-25 refactor(stm32g0): remove unnecessary include
2025-11-27 refactor(stm32g0): remove unnecessary variable
2025-12-01 fix(stm32g0): fix default makefile target
2025-12-06 chore: fix common build tasks
2025-12-06 chore(tool): animation python wrapper
2025-12-08 chore: fix compilation on windows
2025-12-09 feat(tool): add controls to change animation parameters
2025-12-11 feat(tool): add status information
2025-12-11 feat(tool): implement native animation state observers
2025-12-11 feat(tool): improve animation rendering timing
2026-01-09 docs(stm32g0): add README with debugger wiring
2026-01-09 feat(stm32g0): add option to re-configure LED Controller's correction
2026-01-09 fix(stm32g0): improved shifting color animation
2026-01-09 build: do not auto-insert includes
2026-01-09 feat(tool): add command line arguments to select animation
2026-01-09 refactor: add animation count constant
2026-01-09 refactor(stm32g0): refactor Shifting Color animation to use color themes
2026-01-09 chore: add task to clean clangd data
2026-01-09 refactor(stm32g0): refactor Lights animation to use color themes
2026-01-09 feat(stm32g0): add Lights animation
2026-01-09 feat(stm32g0): add LED strip modifier
2026-01-09 build: clean-up VSCode workspace settings
2026-01-09 feat(stm32g0): increase the size of the current animation storage
2026-01-11 feat(stm32g0): add starry night Twinkle Animation theme
2026-01-11 refactor(stm32g0): reuse same code for setting a group of animation parameters
2026-01-11 refactor(stm32g0): make standard colors accessible at compile-time
2026-01-14 feat(stm32g0): make Lights Animation more deterministic
2026-01-14 feat(tool): export and use animation names
2026-01-17 Revert "feat(stm32g0): remove I2C test code"
    This reverts commit ff655ee57877ce53605565a11d07ce43392bc4d0.
